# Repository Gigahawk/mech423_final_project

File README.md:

# LitePog

LitePog is a clone of the [Light Pong](https://www.playlightpong.com/) game.

## Folder Structure
- `firmware`: Code Composer Studio workspace containing firmware for the MSP430FR5739
- `mech`: SolidWorks mechanical CAD files
- `pcb`: KiCad electrical CAD files
- `wiring`: WireViz wire harness diagrams and diagrams.net system wiring diagram
- `proposal`: Initial project proposal for MECH 423 written in LaTeX
- `report`: Final project report for MECH 423 written in LaTeX
- `images`: Images for this readme

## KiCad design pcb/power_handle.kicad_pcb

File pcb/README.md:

# LitePog PCB

PCB files for LitePog

## Rev 2 Bring-Up Notes

The following notes refer to [pcb_rev2](https://github.com/Gigahawk/mech423_final_project/tree/pcb_rev2/pcb) (commit hash 8e8a57b).

Hardware has not been validated as of 2021-12-13, however it is likely that this revision will be functional out of the box.

## Rev 1 Bring-Up Notes

The following notes refer to [pcb_rev1](https://github.com/Gigahawk/mech423_final_project/tree/pcb_rev1/pcb) (commit hash f791dd6).

All hardware (with modifications) has been validated as of 2021-11-27.

### Logic Handle (assembled 2021-11-17)
Logic handle was assembled and tested over multiple days:
- 2021-11-17: Initial bring up and testing of all components
- 2021-11-24:
    - Validate Neopixel function with 3.3V logic level
    - Fix transistor connection for button LED

Notes:
- MCU appears to work fine
    - Can be programmed as expected
    - Resonator `Y1` not populated for now, likely not necessary
        - Firmware can rely entirely on DCO
- Power supply works fine
    - Produces 3.3V as expected
- Level shifter doesn't work
    - Level shifter U2 is designed to be connected between open-drain (or push-pull) pins, not to be connected directly to buttons or LEDs.
    - Solutions:
        - Remove/bypass the shifter (**Current solution as of 2021-11-17**)
            - The only strictly 5V level interface is the Neopixel strip, although it is fairly likely to work at 3.3V
            - All other IO is OK to run at 3.3V
            - *EDIT 2021-11-24: Neopixel strip works fine with 3.3V logic signals, level shifter has been removed, and all bypass jumpers set*
        - Use shifters with explicit transfer directions
            - Will need multiple chips, but this will allow all IO to be 5V
        - Only shift the Neopixel data line
            - Minimizes chips, ideal solution for next revision
- LED transistor `Q1` is wired incorrectly
    - Current always flows through body diode regardless of input
    - Solutions:
        - Short `LED-` and `LED1` (*Solution from 2021-11-17*):
            - This inverses the LED on polarity (Set `LED1` to let current flow, high to stop)
            - This sinks 20 mA into the GPIO pin, not ideal.
            - This may cause problems/uneven lighting across the interconnect due to voltage drop.
                - The transistor on the power PCB appears to be correct
        - Flip transistor on PCB (**Current solution as of 2021-11-24**)
            - Pins 1 and 2 need to be swapped (pins on same side of IC), which means pin 3 will be facing the other way. It just so happens that there is a ground pad at approximately the right distance away from the actual transistor footprint that would make this work (or some of the silkscreen can be scratched away)
            - *CORRECTION 2021-11-24: pins 2 and 3 need to be swapped, this was done by rotating IC 180 degrees.*
            *Pin 1 was left floating, which was connected back to R8 with a bodge wire.*
        - Fix transistor configuration in schematic(swap drain and source)
            - ideal solution for next revision
- *EDIT 2021-12-06: LED strip connector `JNPX1` should be moved towards the center by 0.5 to 1mm to avoid interference with the casing.*

### Power Handle
Power handle was assembled over multiple days:
- 2021-11-26: bring up and testing of critical components (boost, charging, protection, in that order)
- 2021-11-27: assemble misc components (connectors, battery holder, button circuitry)
- 2021-12-09: Final testing of safety features

Notes:
- Boost circuit works as designed, capable of producing high current (> 1A continuous for 10 seconds)
- Boost circuit can not be turned off
    - The datasheet for PAM2423 indicates that setting the `EN` pin low only disables the IC's boosting function, it does not turn off the output since there is a direct path from input to output via the inductor and diode.
    - Solutions:
        - Use switch to cut off input current (**Current solution as of 2021-11-26**)
            - Done by cutting the traces going to the input, and running wires to `SW1`.
                - `SW1` is already connected to `BATT+` to drive the `EN` pin, add an extra wire to allow high current flow
            - The EG1224 is only rated for 0.5A, finding higher current switches in this form factor is hard
                - EG2219 is a DPDT switch rated for 0.5A per pole, which can theoretically be combined for 1A total current, but this is still impractical because the input must provide more than 1A current at peak loads
                - Testing at 1A output current (~ 2A input current) seems to be fine (tested for ~10 seconds)
            - This is the simplest solution for this revision, since it does not require `EN` to be rewired, nor does it allow the boost converter to continually drain the battery from quiescent current.
            - There is a risk of arcing if switch is disconnected during high load, although this has not been observed, and should never happen in normal operation
        - Use switch to cut off output current
            - Similar issues to cutting off input current, although current requirements on the output are lower
            - Boost converter will be constantly on, and drawing quiescent current from battery
            - There is a risk of arcing if switch is disconnected during high load, although this has not been observed, and should never happen in normal operation
        - Use MOSFET to switch input current
            - Switch input from high side using a PMOS
            - Ideal solution for next revision
- Charging circuit appears to work as expected
    - LED comes on when plugged in and battery is below max voltage
    - LED turns off when max voltage is reached
    - *EDIT 2021-12-09: Full discharge and charge cycle tested. Charging cutoff occurred at 4.2V as expected*
- Protection circuit appears to work as expected
    - Datasheet for BQ2970 indicates that it must be bootstrapped the first time by connecting a charger to the battery, which was observed
    - *Note: protection features are largely untested*
        - Over discharge current protection is set high enough that it cannot trip
            - This is intentional, we want to allow the battery to provide as much current as necessary for the boost converter
            - A battery capable of providing the necessary current without overheating is being used
        - Short circuit protection is untested
            - This would involve shorting `BATT+` to ground, which is unlikely to happen in regular operation
            - This safety feature is typically intended for standalone battery protection boards that provide user accessible output terminals that could be accidentally shorted
        - Under voltage protection is untested
            - It is time-consuming to wait for the battery to completely drain while monitoring the voltage to ensure that the cutoff protection works.
            - Periodic checking of the battery voltage during firmware development should take place to ensure the battery voltage is within safe levels
            - *EDIT 2021-12-09: Full discharge and charge cycle tested.*
                - Output was shut off at a safe voltage (VBAT ~2.9V when measured, but it may have risen slightly due to hysteresis)
                - It is unclear which chip is actually responsible for cutting off the battery, both the PAM2423 boost converter and the BQ29703DSET protection chip is rated for an under voltage lockout of 2.5V, although it is likely both chips are working as expected.
        - Over voltage protection is untested
            - The charging circuit stops charging the battery prior to the over voltage protection threshold
        - Over charge current protection is untested
            - The charge current of the charging circuit is fixed at 500mA, and should never be high enough to trigger over charge current protection
- Bypass diode `D2` is left unpopulated
    - Theoretically it should be safe to populate, however it is unknown if this will cause adverse behavior with the boost circuit.
    - Populating this diode will prevent the output from being turned off with the switch when `VBUS` is present
- Aluminum capacitors `C10` and `C1` are not structurally sound
    - Should be reinforced with hot glue

### Button Harness (Assembled 2021-11-24)
- Works as expected

### Neopixel Strip (Assembled 2021-11-24)
- Removing provided connectors is rather hard
    - Nearly damaged the pads while removing old joints
    - Simpler solution for next revision is to order more LEDs than required and cut off first one to access unsoldered pads

### Interconnect Harness (Assembled 2021-11-24)
- Works as expected
- Very time-consuming to assemble, set aside more time to do this next revision

### Mock Power Handle (Assembled 2021-11-27)
- Assembled board with bypass diode `D2` connecting the USB connector directly to `VCC`, and button circuitry for use in firmware testing.

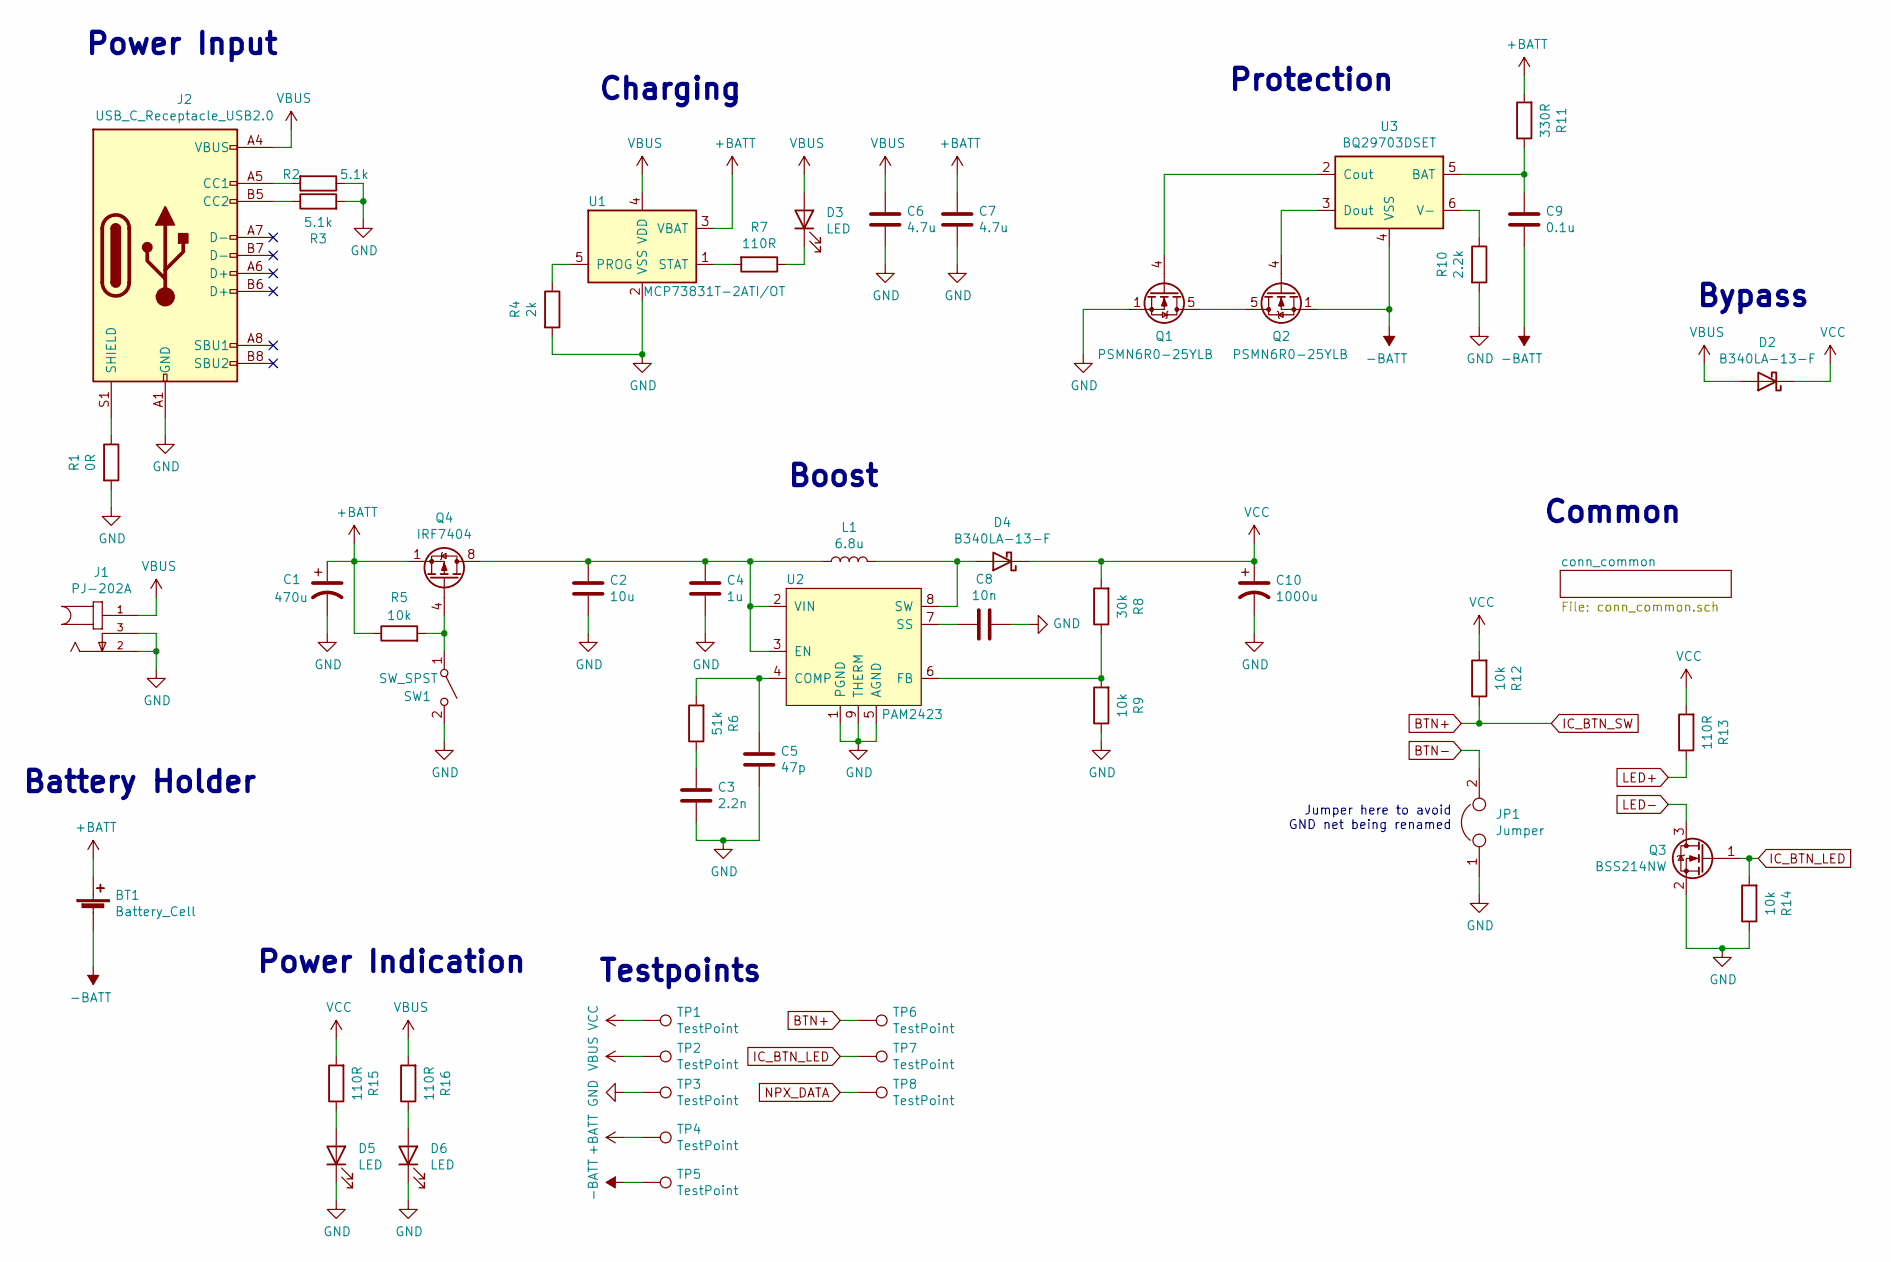
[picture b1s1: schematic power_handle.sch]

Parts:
BT1: Battery_Cell; BatteryHolder_Keystone_1042_1x18650; Digikey 36-1042-ND
C1: 470u; CP_Elec_8x10; Digikey 732-6451-1-ND
C2: 10u; C_0805_2012Metric; Digikey 1276-6456-1-ND
C3: 2.2n; C_0805_2012Metric; Digikey 1276-2484-1-ND
C4: 1u; C_0805_2012Metric; Digikey 1276-1026-1-ND
C5: 47p; C_0805_2012Metric; Digikey 709-1175-1-ND
C6, C7: 4.7u; C_0805_2012Metric; Digikey 1276-1259-1-ND
C8: 10n; C_0805_2012Metric; Digikey 478-1383-1-ND
C9: 0.1u; C_0805_2012Metric; Digikey 478-10836-1-ND
C10: 1000u; CP_Elec_10x12.6; Digikey 493-13738-1-ND
D2, D4: B340LA-13-F; D_SMA; Digikey 641-1258-1-ND
D3, D5, D6: LED; LED_0603_1608Metric; Digikey 160-1832-1-ND
J1: PJ-202A; CUI_PJ-202A; PART_REV 1.02; Digikey CP-202A-ND
J2: USB_C_Receptacle_USB2.0; UJC-HP-3-SMT-TR; Digikey 2223-UJC-HP-3-SMT-CT-ND
JP1: Jumper; SolderJumper-2_P1.3mm_Bridged2Bar_Pad1.0x1.5mm
L1: 6.8u; ASPI-0630LR-6R8M-T15; Digikey 535-13041-1-ND
Q1, Q2: PSMN6R0-25YLB; LFPAK56; Digikey 1727-6497-1-ND
Q3: BSS214NW; SOT-323_SC-70; Digikey BSS214NWH6327XTSA1CT-ND
Q4: IRF7404; SOIC-8_3.9x4.9mm_P1.27mm; Digikey IRF7404PBFCT-ND
R1: 0R; R_0805_2012Metric; Digikey RMCF0805ZT0R00CT-ND
R2, R3: 5.1k; R_0805_2012Metric; Digikey A126379CT-ND
R4: 2k; R_0805_2012Metric; Digikey RG20N2.0KWCT-ND
R5, R9, R12, R14: 10k; R_0805_2012Metric; Digikey RMCF0805JT10K0CT-ND
R6: 51k; R_0805_2012Metric; Digikey A126373CT-ND
R7, R13, R15, R16: 110R; R_0805_2012Metric; Digikey RMCF0805JT110RCT-ND
R8: 30k; R_0805_2012Metric; Digikey 13-RT0805FRE0730KLCT-ND
R10: 2.2k; R_0805_2012Metric; Digikey A106060CT-ND
R11: 330R; R_0805_2012Metric; Digikey A130131CT-ND
SW1: SW_SPST; SW_E-Switch_EG1224_SPDT_Angled; Digikey EG2585-ND
TP1, TP2, TP3, TP4, TP5, TP6, TP7, TP8: TestPoint; TestPoint_Pad_2.0x2.0mm
U1: MCP73831T-2ATI/OT; SOT-23-5; Digikey MCP73831T-2ATI/OTCT-ND
U2: PAM2423; HSOP-8-1EP_3.9x4.9mm_P1.27mm_EP2.41x3.1mm_HandSolderThermal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; Digikey PAM2423AECADJRDICT-ND
U3: BQ29703DSET; WSON-6_1.5x1.5mm_P0.5mm; Digikey 296-37960-1-ND

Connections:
+BATT: BT1.1 (+), C1.1, C7.1, Q4.1 (S), Q4.2 (S), Q4.3 (S), R5.1, R11.2, TP4.1, U1.3 (VBAT)
-BATT: BT1.2 (-), C9.2, Q2.1 (S), Q2.2 (S), Q2.3 (S), TP5.1, U3.4 (VSS)
BTN+: R12.1, TP6.1; also elsewhere on the board
BTN-: JP1.2; also elsewhere on the board
GND: C1.2, C2.1, C3.1, C4.1, C5.2, C6.2, C7.2, C8.1, C10.2, D5.1 (K), D6.1 (K), J1.2, J1.3, J2.A1 (GND), J2.A12 (GND), J2.B1 (GND), J2.B12 (GND), JP1.1, Q1.1 (S), Q1.2 (S), Q1.3 (S), Q3.2 (S), R1.2, R2.1, R3.2, R4.2, R9.1, R10.2, R14.1, SW1.2 (B), TP3.1, U1.2 (VSS), U2.1 (PGND), U2.5 (AGND), U2.9 (THERM); also elsewhere on the board
IC_BTN_LED: Q3.1 (G), R14.2, TP7.1; also elsewhere on the board
LED+: R13.1; also elsewhere on the board
LED-: Q3.3 (D); also elsewhere on the board
NPX_DATA: TP8.1; also elsewhere on the board
unnamed: C2.2, C4.2, L1.1, Q4.5 (D), Q4.6 (D), Q4.7 (D), Q4.8 (D), U2.2 (VIN), U2.3 (EN)
unnamed: C3.2, R6.1
unnamed: C5.1, R6.2, U2.4 (COMP)
unnamed: C8.2, U2.7 (SS)
unnamed: C9.1, R11.1, U3.5 (BAT)
unnamed: D3.1 (K), R7.1
unnamed: D4.2 (A), L1.2, U2.8 (SW)
unnamed: D5.2 (A), R15.1
unnamed: D6.2 (A), R16.1
unnamed: J2.A5 (CC1), R2.2
unnamed: J2.B5 (CC2), R3.1
unnamed: J2.S1 (SHIELD), R1.1
unnamed: Q1.4 (G), U3.2 (Cout)
unnamed: Q1.5 (D), Q2.5 (D)
unnamed: Q2.4 (G), U3.3 (Dout)
unnamed: Q4.4 (G), R5.2, SW1.1 (A)
unnamed: R4.1, U1.5 (PROG)
unnamed: R7.2, U1.1 (STAT)
unnamed: R8.1, R9.2, U2.6 (FB)
unnamed: R10.1, U3.6 (V-)
VBUS: C6.1, D2.2 (A), D3.2 (A), J1.1, J2.A4 (VBUS), J2.A9 (VBUS), J2.B4 (VBUS), J2.B9 (VBUS), R16.2, TP2.1, U1.4 (VDD)
VCC: C10.1, D2.1 (K), D4.1 (K), R8.2, R12.2, R13.2, R15.2, TP1.1; also elsewhere on the board

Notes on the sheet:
Power Input
Charging
Protection
Boost
Battery Holder
Common
Power Indication
Testpoints
Jumper here to avoid GND net being renamed
Bypass

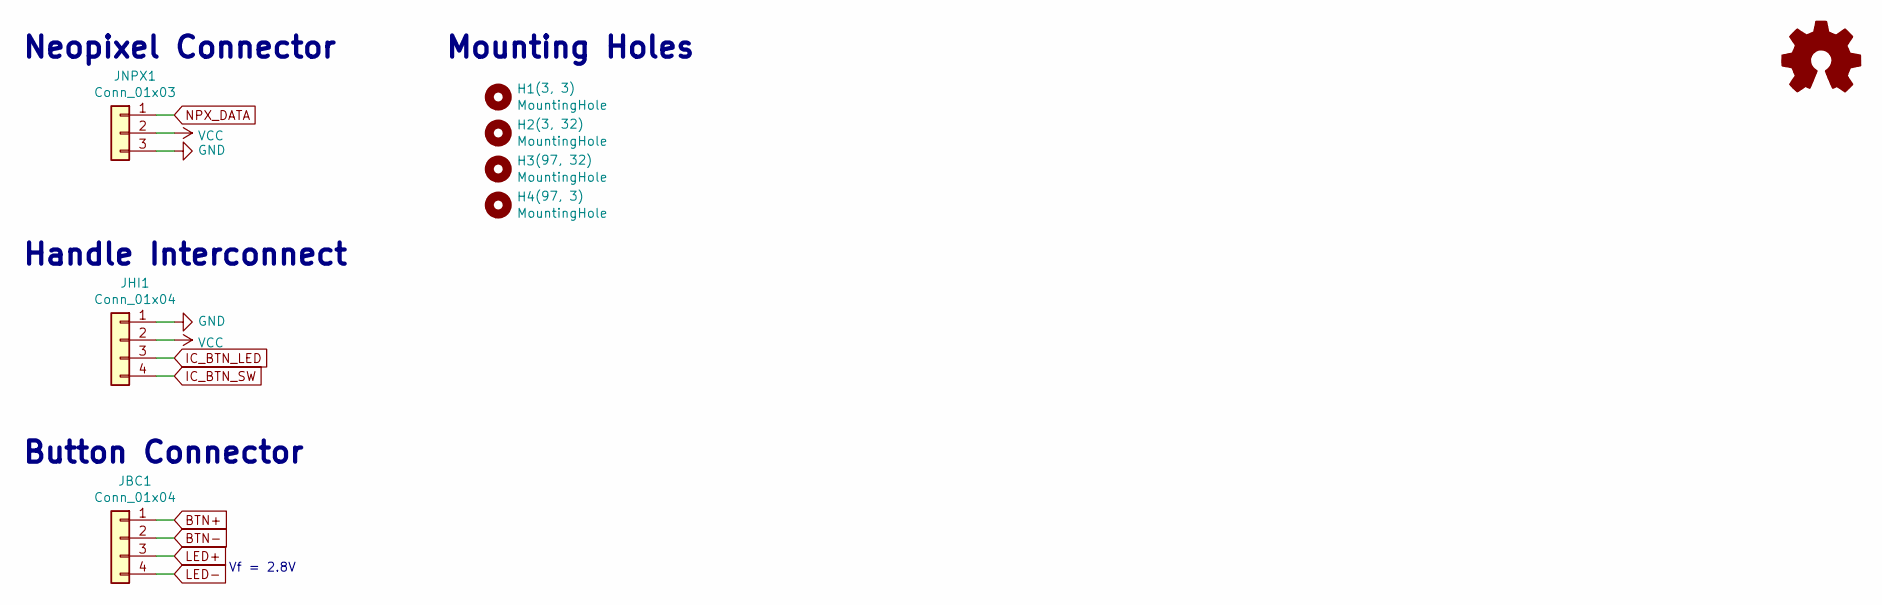
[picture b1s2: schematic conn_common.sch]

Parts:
H1, H2, H3, H4: MountingHole; MountingHole_2.7mm_M2.5
JBC1: Conn_01x04; JST_SH_SM04B-SRSS-TB_1x04-1MP_P1.00mm_Horizontal; Digikey SM04B-SRSS-TB
JHI1: Conn_01x04; JST_SH_SM04B-SRSS-TB_1x04-1MP_P1.00mm_Horizontal; Digikey SM04B-SRSS-TB
JNPX1: Conn_01x03; JST_PH_S3B-PH-SM4-TB_1x03-1MP_P2.00mm_Horizontal; Digikey 455-1750-1-ND
LOGO1: Logo_Open_Hardware_Small; OSHW-Logo_5.7x6mm_SilkScreen

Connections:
BTN+: JBC1.1, JHI1.4; also elsewhere on the board
BTN-: JBC1.2; also elsewhere on the board
GND: JHI1.1, JNPX1.3; also elsewhere on the board
IC_BTN_LED: JHI1.3; also elsewhere on the board
LED+: JBC1.3; also elsewhere on the board
LED-: JBC1.4; also elsewhere on the board
NPX_DATA: JNPX1.1; also elsewhere on the board
VCC: JHI1.2, JNPX1.2; also elsewhere on the board

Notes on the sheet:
Neopixel Connector
Handle Interconnect
Button Connector
Vf = 2.8V
Mounting Holes

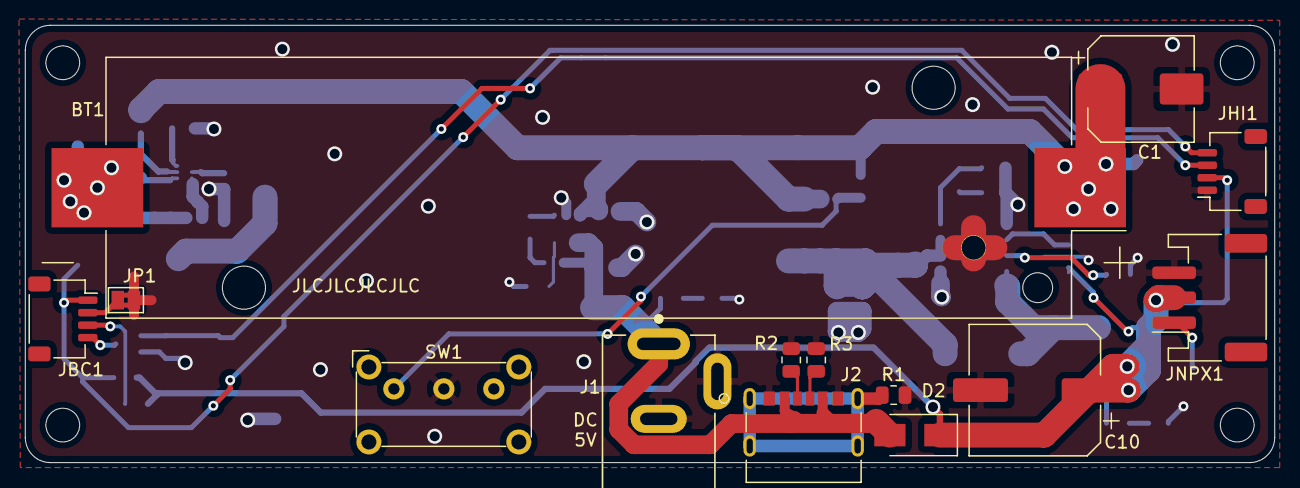
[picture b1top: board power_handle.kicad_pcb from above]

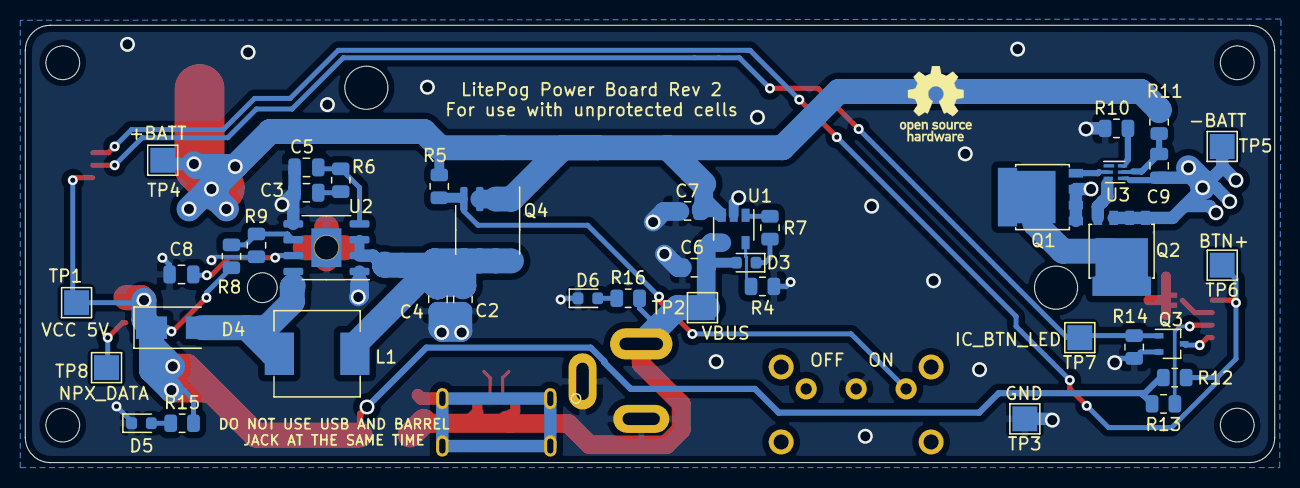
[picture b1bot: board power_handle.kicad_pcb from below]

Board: 2 copper layers, 100.0 x 35.0 mm, 60 parts (42 on the bottom side), 31 nets.

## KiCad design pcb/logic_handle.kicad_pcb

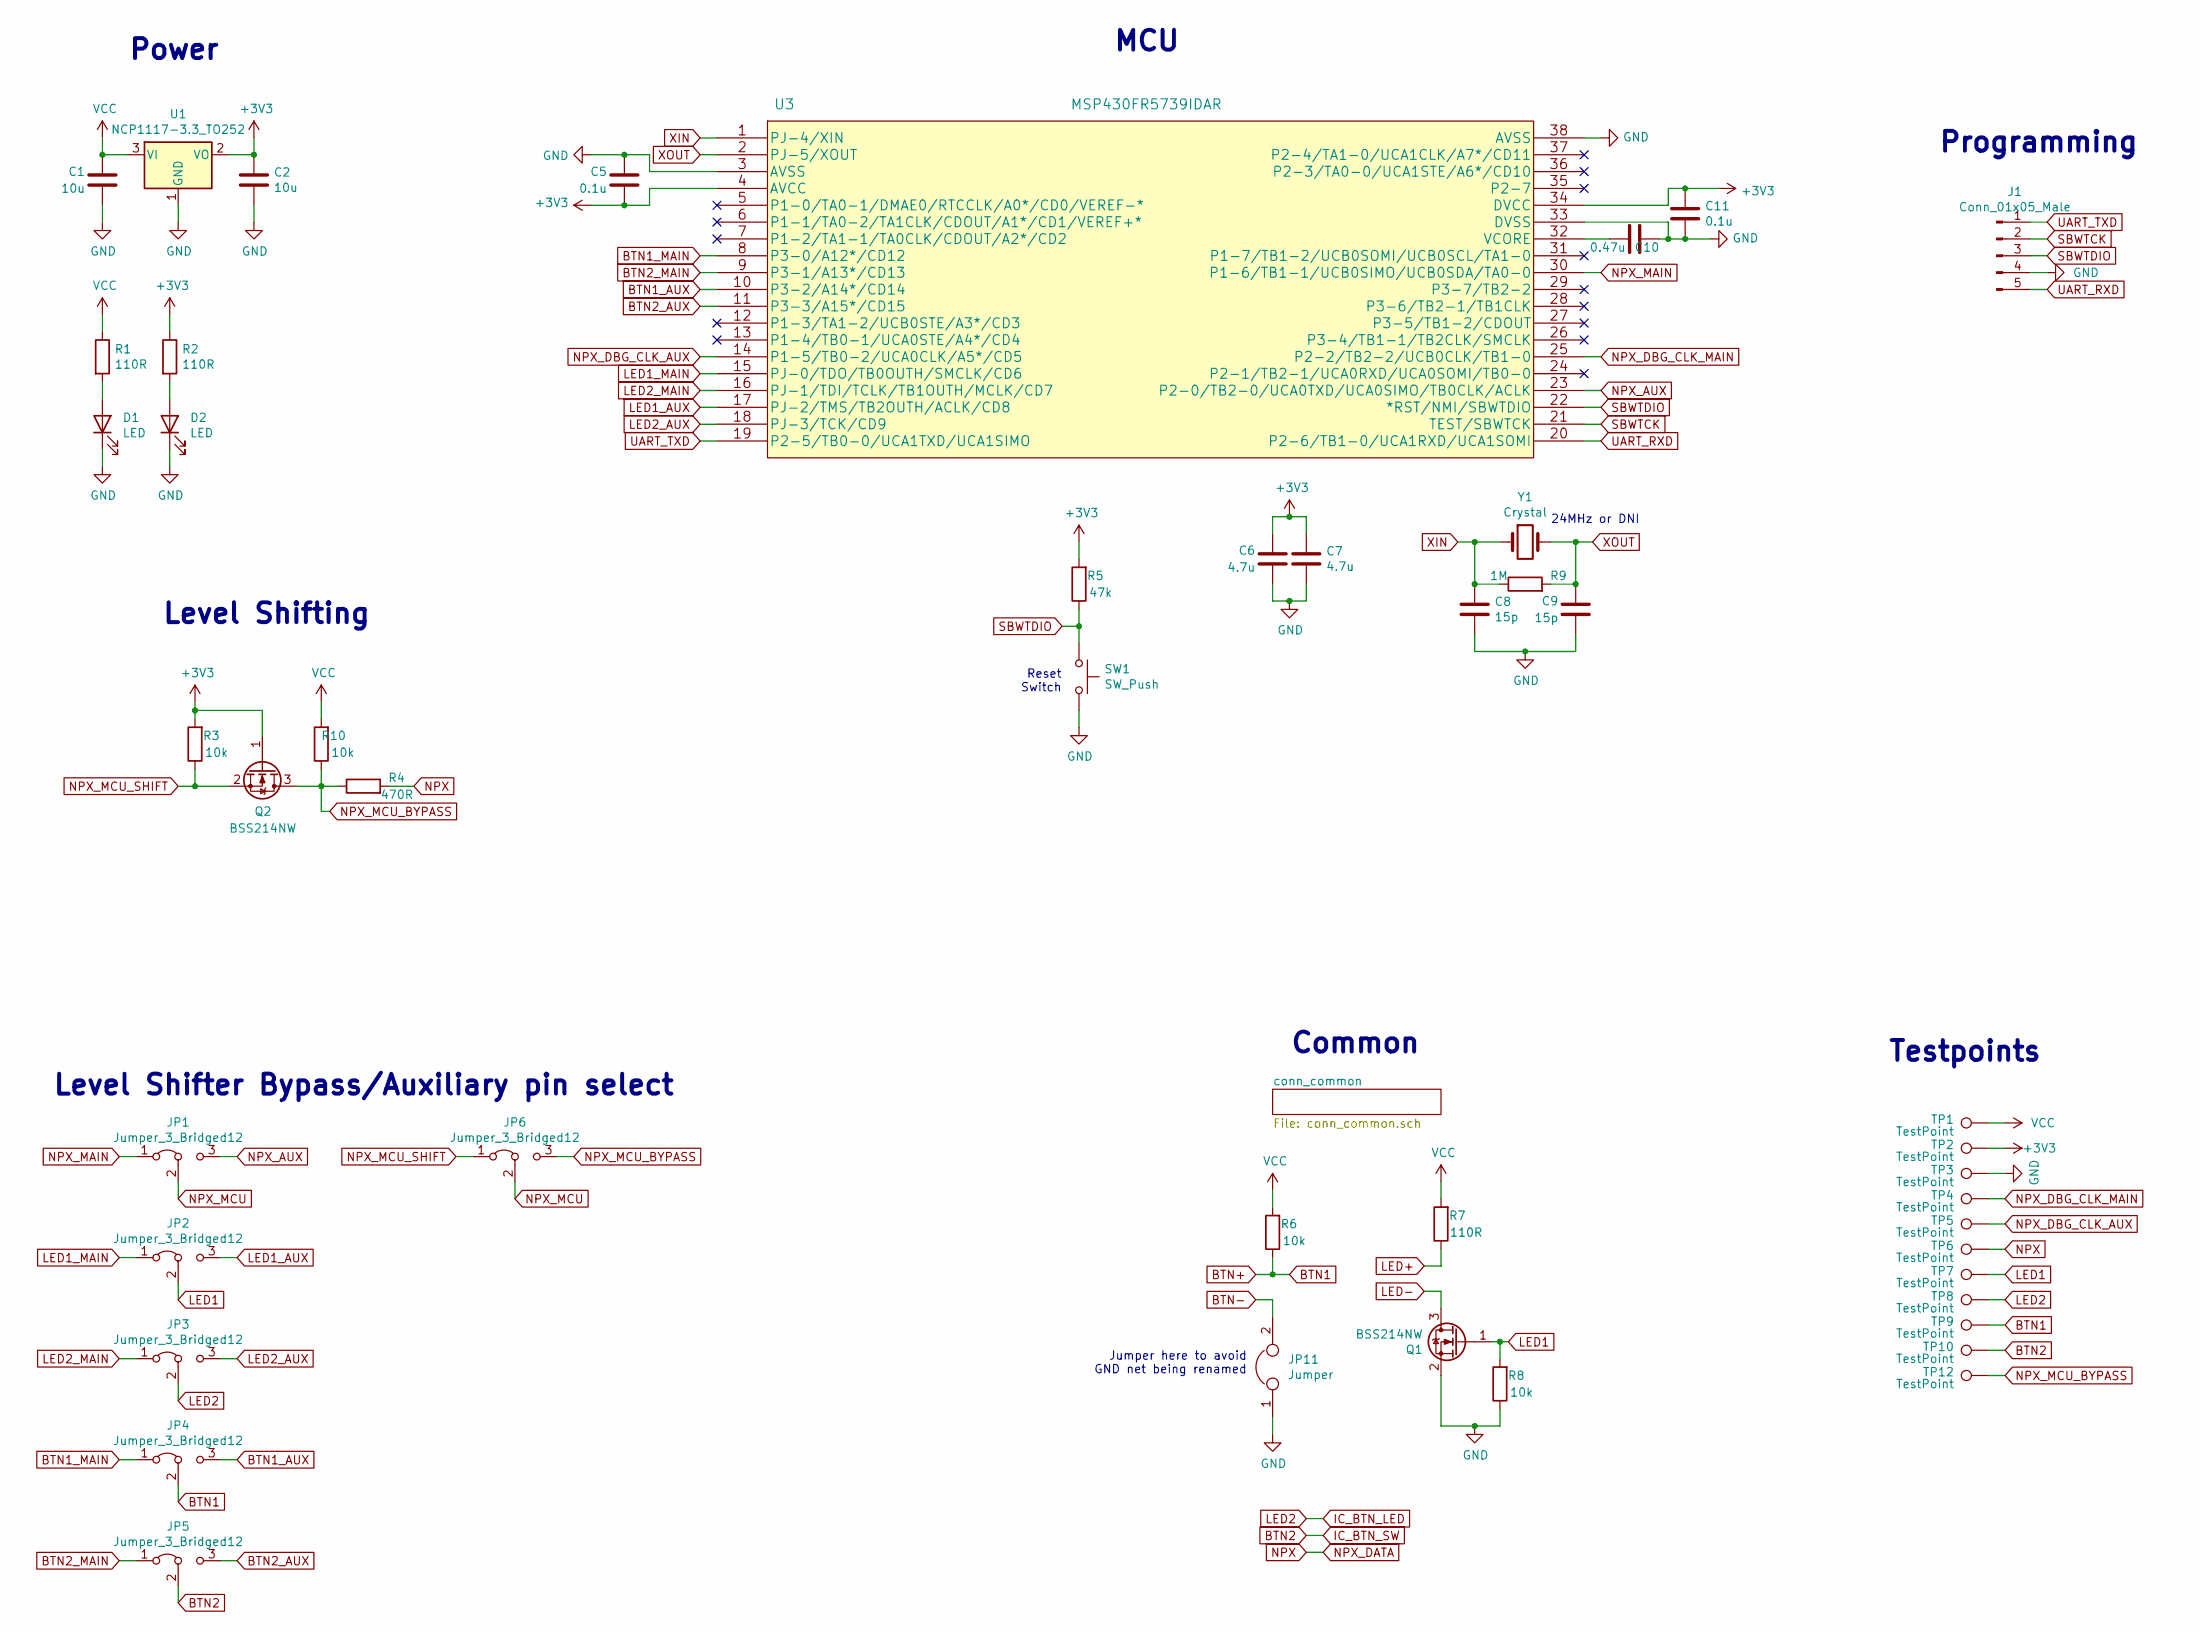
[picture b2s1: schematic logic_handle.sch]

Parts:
C1, C2: 10u; C_0805_2012Metric; Digikey 1276-6456-1-ND
C5, C11: 0.1u; C_0805_2012Metric; Digikey 478-10836-1-ND
C6, C7: 4.7u; C_0805_2012Metric; Digikey 1276-1259-1-ND
C8, C9: 15p; C_0805_2012Metric; Digikey 478-1306-1-ND
C10: 0.47u; C_0805_2012Metric; Digikey 478-10438-1-ND
D1, D2: LED; LED_0603_1608Metric; Digikey 160-1832-1-ND
J1: Conn_01x05_Male; PinHeader_1x05_P2.54mm_Vertical
JP1, JP2, JP3, JP4, JP5, JP6: Jumper_3_Bridged12; SolderJumper-3_P1.3mm_Bridged2Bar12_Pad1.0x1.5mm
JP11: Jumper; SolderJumper-2_P1.3mm_Bridged2Bar_Pad1.0x1.5mm
Q1, Q2: BSS214NW; SOT-323_SC-70; Digikey BSS214NWH6327XTSA1CT-ND
R1, R2, R7: 110R; R_0805_2012Metric; Digikey RMCF0805JT110RCT-ND
R3, R6, R8, R10: 10k; R_0805_2012Metric; Digikey RMCF0805JT10K0CT-ND
R4: 470R; R_0805_2012Metric; Digikey A129745CT-ND
R5: 47k; R_0805_2012Metric; Digikey A130144CT-ND
R9: 1M; R_0805_2012Metric; Digikey A106058CT-ND
SW1: SW_Push; SW_SPST_TL3342; Digikey EG5470CT-ND
TP1, TP2, TP3, TP4, TP5, TP6, TP7, TP8, TP9, TP10, TP12: TestPoint; TestPoint_Pad_2.0x2.0mm
U1: NCP1117-3.3_TO252; TO-252-2; Digikey NCP1117ST33T3GOSCT-ND
U3: MSP430FR5739IDAR; Digikey 296-29235-1-ND
Y1: Crystal; Crystal_SMD_AWSZT-CV-2Pin_3.7x3.1mm; Digikey 535-10028-2-ND

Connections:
+3V3: C2.1, C5.1, C6.2, C7.1, C11.1, Q2.1 (G), R2.1, R3.2, R5.2, TP2.1, U1.2 (VO), U3.4 (AVCC), U3.34 (DVCC)
BTN1_AUX: JP4.3 (B), U3.10 (P3-2/A14*/CD14)
BTN1_MAIN: JP4.1 (A), U3.8 (P3-0/A12*/CD12)
BTN2: JP5.2 (C), TP10.1; also elsewhere on the board
BTN2_AUX: JP5.3 (B), U3.11 (P3-3/A15*/CD15)
BTN2_MAIN: JP5.1 (A), U3.9 (P3-1/A13*/CD13)
BTN+: JP4.2 (C), R6.1, TP9.1; also elsewhere on the board
BTN-: JP11.2; also elsewhere on the board
GND: C1.1, C2.2, C5.2, C6.1, C7.2, C8.2, C9.1, C10.2, C11.2, D1.1 (K), D2.1 (K), J1.4, JP11.1, Q1.2 (S), R8.1, SW1.2, TP3.1, U1.1 (GND), U3.3 (AVSS), U3.33 (DVSS), U3.38 (AVSS); also elsewhere on the board
IC_BTN_LED: JP3.2 (C), TP8.1; also elsewhere on the board
LED1: JP2.2 (C), Q1.1 (G), R8.2, TP7.1
LED1_AUX: JP2.3 (B), U3.17 (PJ-2/TMS/TB2OUTH/ACLK/CD8)
LED1_MAIN: JP2.1 (A), U3.15 (PJ-0/TDO/TB0OUTH/SMCLK/CD6)
LED2_AUX: JP3.3 (B), U3.18 (PJ-3/TCK/CD9)
LED2_MAIN: JP3.1 (A), U3.16 (PJ-1/TDI/TCLK/TB1OUTH/MCLK/CD7)
LED+: R7.1; also elsewhere on the board
LED-: Q1.3 (D); also elsewhere on the board
NPX: R4.2, TP6.1; also elsewhere on the board
NPX_AUX: JP1.3 (B), U3.23 (P2-0/TB2-0/UCA0TXD/UCA0SIMO/TB0CLK/ACLK)
NPX_DBG_CLK_AUX: TP5.1, U3.14 (P1-5/TB0-2/UCA0CLK/A5*/CD5)
NPX_DBG_CLK_MAIN: TP4.1, U3.25 (P2-2/TB2-2/UCB0CLK/TB1-0)
NPX_MAIN: JP1.1 (A), U3.30 (P1-6/TB1-1/UCB0SIMO/UCB0SDA/TA0-0)
NPX_MCU: JP1.2 (C), JP6.2 (C)
NPX_MCU_BYPASS: JP6.3 (B), Q2.3 (D), R4.1, R10.1, TP12.1
NPX_MCU_SHIFT: JP6.1 (A), Q2.2 (S), R3.1
unnamed: C10.1, U3.32 (VCORE)
unnamed: D1.2 (A), R1.2
unnamed: D2.2 (A), R2.2
SBWTCK: J1.2, U3.21 (TEST/SBWTCK)
SBWTDIO: J1.3, R5.1, SW1.1, U3.22 (*RST/NMI/SBWTDIO)
UART_RXD: J1.5, U3.20 (P2-6/TB1-0/UCA1RXD/UCA1SOMI)
UART_TXD: J1.1, U3.19 (P2-5/TB0-0/UCA1TXD/UCA1SIMO)
VCC: C1.2, R1.1, R6.2, R7.2, R10.2, TP1.1, U1.3 (VI); also elsewhere on the board
XIN: C8.1, R9.1, U3.1 (PJ-4/XIN), Y1.1
XOUT: C9.2, R9.2, U3.2 (PJ-5/XOUT), Y1.2

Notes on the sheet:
Level Shifting
MCU
Power
Reset Switch
Level Shifter Bypass/Auxiliary pin select
Jumper here to avoid GND net being renamed
Programming
24MHz or DNI
Common
Testpoints

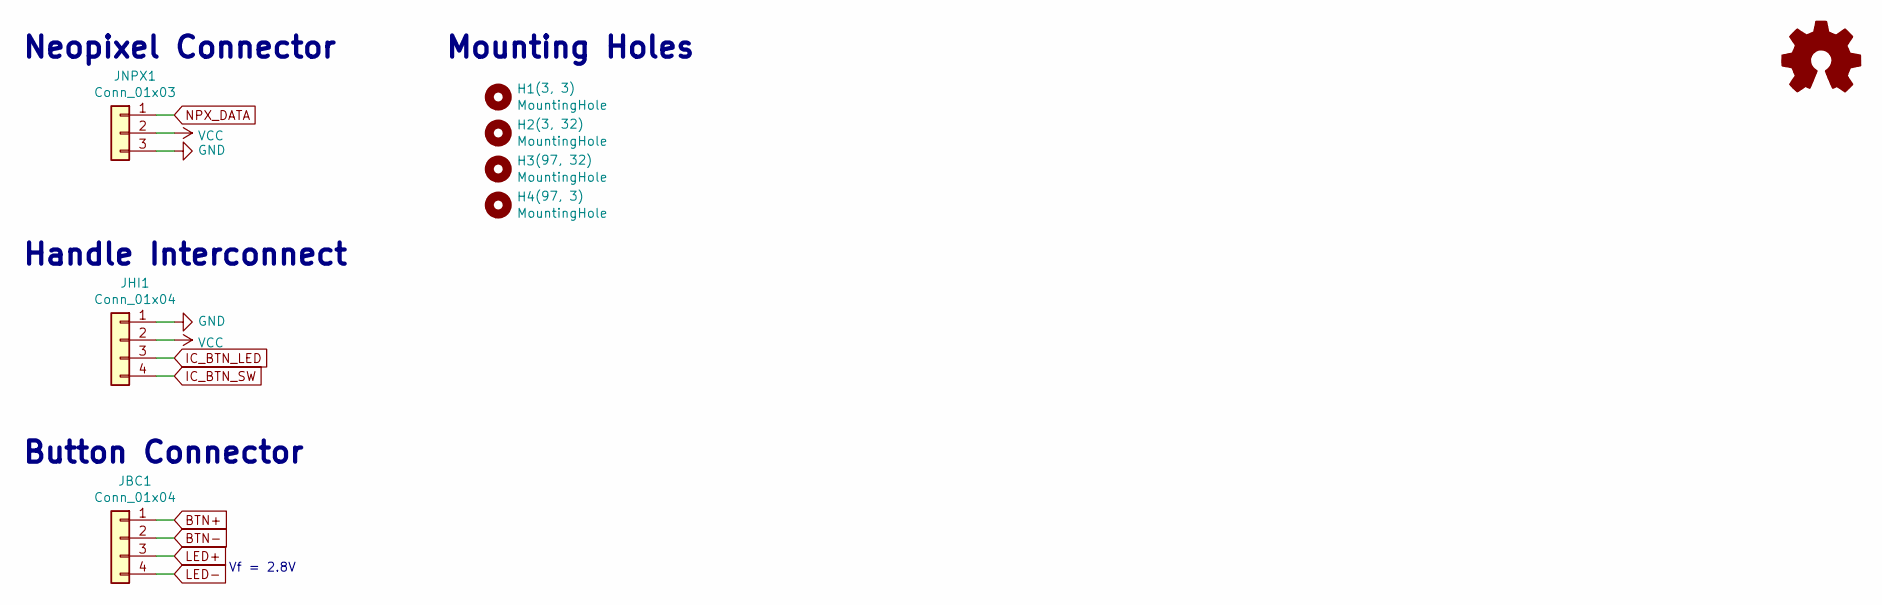
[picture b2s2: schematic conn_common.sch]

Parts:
H1, H2, H3, H4: MountingHole; MountingHole_2.7mm_M2.5
JBC1: Conn_01x04; JST_SH_SM04B-SRSS-TB_1x04-1MP_P1.00mm_Horizontal; Digikey SM04B-SRSS-TB
JHI1: Conn_01x04; JST_SH_SM04B-SRSS-TB_1x04-1MP_P1.00mm_Horizontal; Digikey SM04B-SRSS-TB
JNPX1: Conn_01x03; JST_PH_S3B-PH-SM4-TB_1x03-1MP_P2.00mm_Horizontal; Digikey 455-1750-1-ND
LOGO1: Logo_Open_Hardware_Small; OSHW-Logo_5.7x6mm_SilkScreen

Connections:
BTN2: JHI1.4; also elsewhere on the board
BTN+: JBC1.1; also elsewhere on the board
BTN-: JBC1.2; also elsewhere on the board
GND: JHI1.1, JNPX1.3; also elsewhere on the board
IC_BTN_LED: JHI1.3; also elsewhere on the board
LED+: JBC1.3; also elsewhere on the board
LED-: JBC1.4; also elsewhere on the board
NPX: JNPX1.1; also elsewhere on the board
VCC: JHI1.2, JNPX1.2; also elsewhere on the board

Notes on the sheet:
Neopixel Connector
Handle Interconnect
Button Connector
Vf = 2.8V
Mounting Holes

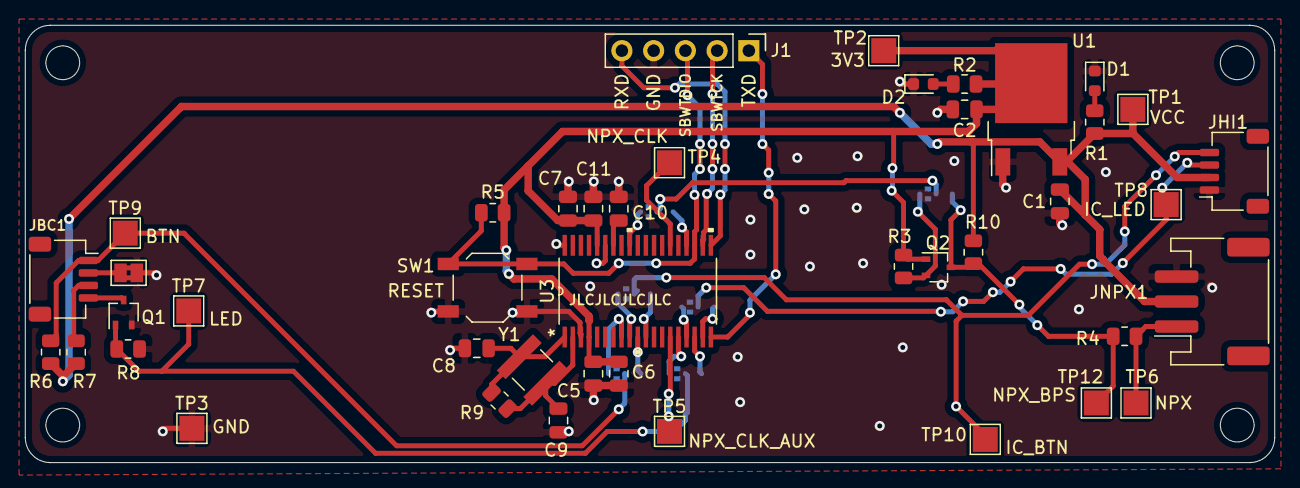
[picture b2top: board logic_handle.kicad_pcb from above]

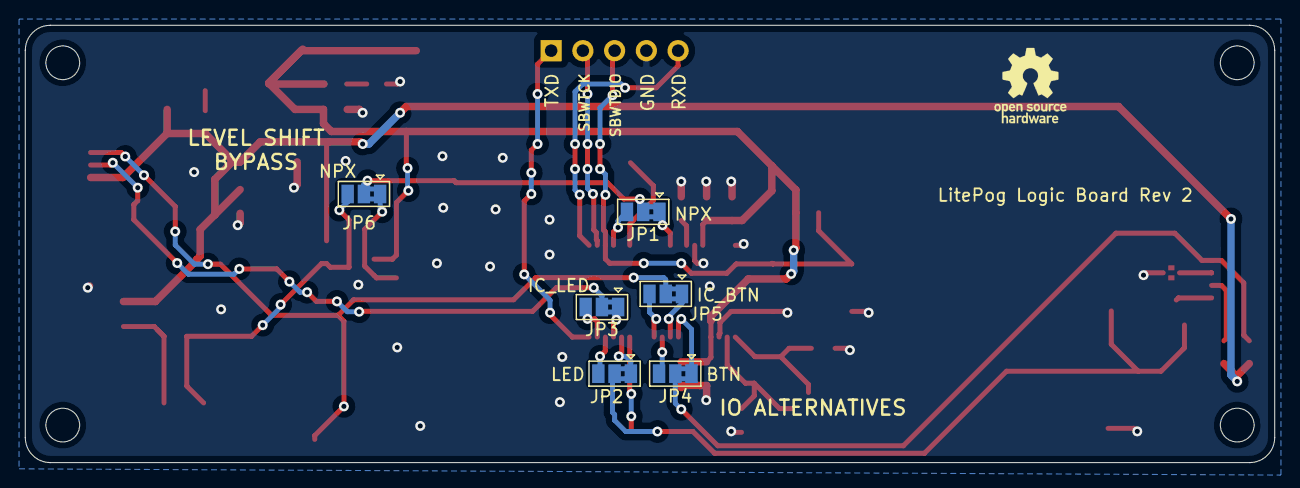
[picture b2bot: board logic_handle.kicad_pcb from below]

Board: 2 copper layers, 100.0 x 35.0 mm, 54 parts (7 on the bottom side), 35 nets.

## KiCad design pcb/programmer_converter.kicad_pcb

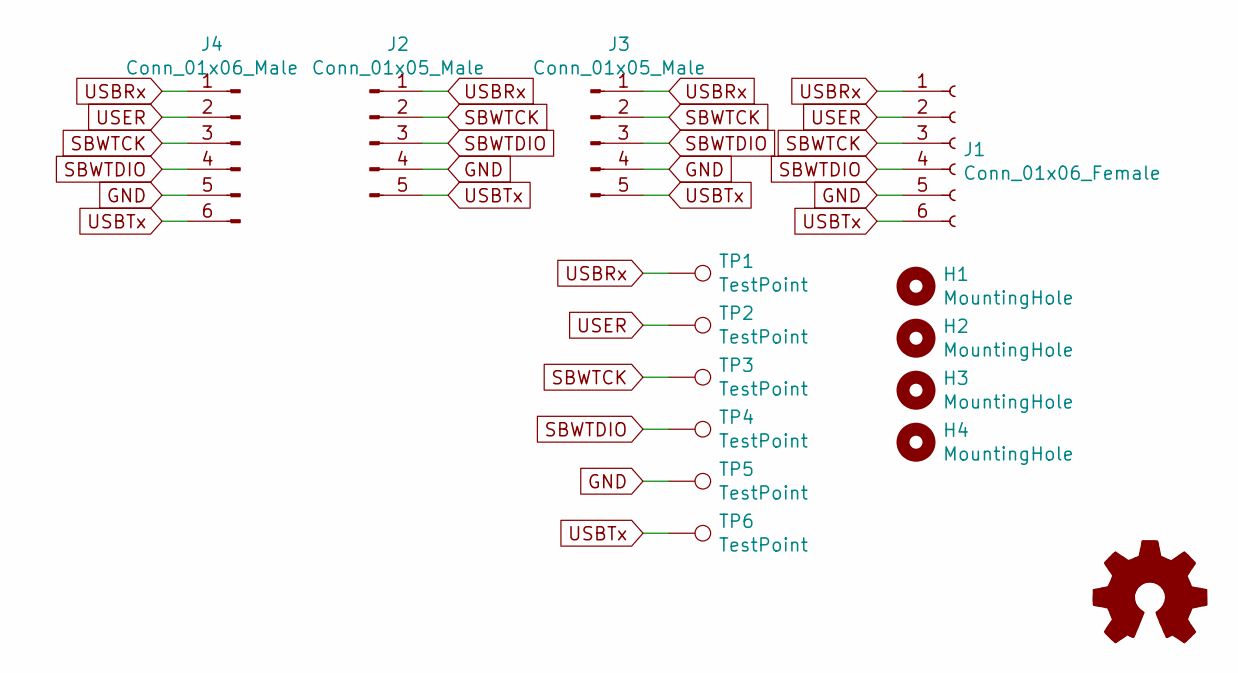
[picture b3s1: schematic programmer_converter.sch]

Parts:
H1, H2, H3, H4: MountingHole; MountingHole_2.7mm_M2.5
J1: Conn_01x06_Female; 851-87-006-20-001101
J2, J3: Conn_01x05_Male; PinHeader_1x05_P2.54mm_Vertical
J4: Conn_01x06_Male; PinHeader_1x06_P1.27mm_Horizontal
LOGO1: Logo_Open_Hardware_Small; OSHW-Logo_5.7x6mm_SilkScreen
TP1, TP2, TP3, TP4, TP5, TP6: TestPoint; TestPoint_Pad_2.0x2.0mm

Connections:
GND: J1.5, J2.4, J3.4, J4.5, TP5.1
SBWTCK: J1.3, J2.2, J3.2, J4.3, TP3.1
SBWTDIO: J1.4, J2.3, J3.3, J4.4, TP4.1
USBRx: J1.1, J2.1, J3.1, J4.1, TP1.1
USBTx: J1.6, J2.5, J3.5, J4.6, TP6.1
USER: J1.2, J4.2, TP2.1

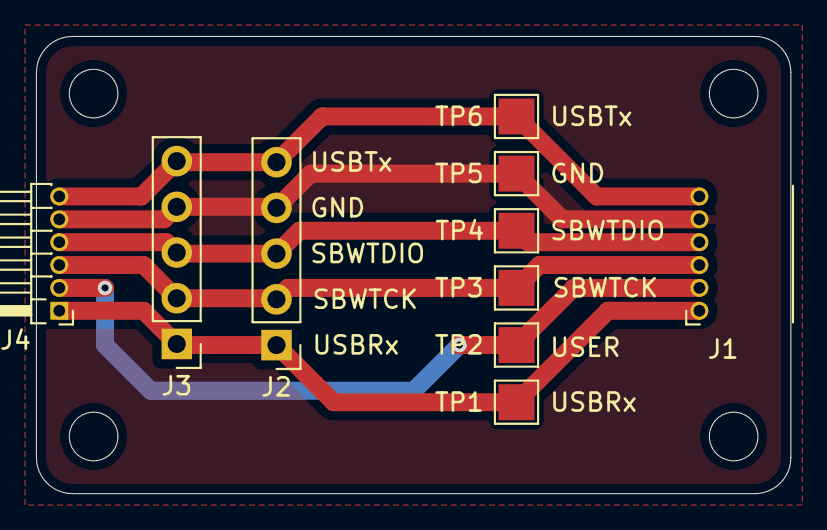
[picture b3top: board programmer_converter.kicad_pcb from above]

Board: 2 copper layers, 41.9 x 25.4 mm, 15 parts (1 on the bottom side), 6 nets.

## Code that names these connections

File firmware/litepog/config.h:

/*
 * config.h
 *
 *  Created on: Nov 16, 2021
 *      Author: Jasper
 */

#ifndef CONFIG_H_
#define CONFIG_H_

// Number of LEDs in Neopixel strip
#define NPX_NUM_LEDS 30

// Index of middle LED
#define NPX_MID_IDX (NPX_NUM_LEDS/2)

// True if even number of LEDs
#define NPX_EVEN_LEDS (!(NPX_NUM_LEDS % 2))

// Seed for pseudo-random number generator
#define PRNG_SEED 0xB00B

// Time to wait between allowing button edges during game select
#define GAME_SELECT_DEBOUNCE_TIME 20

// Width of game selection menu indicator
#define GAME_SELECT_WIDTH 6

// Time between demo animation frames
#define DEMO_INTERVAL 10

// Frame divisor for pong demo animation
#define DEMO_PONG_INTERVAL_DIV 4

// Frame divisor for ping pong demo animation
#define DEMO_PINGPONG_INTERVAL_DIV 4

// Frame divisor for tug o' war demo animation
#define DEMO_TUGOWAR_INTERVAL_DIV 2

// Chance of ball being returned each frame of ping pong demo animation (1/N)
#define DEMO_PINGPONG_RETURN_RATE 9

// Width of the demo animation
#define DEMO_WIDTH 8

#define DEMO_MIN_IDX (NPX_MID_IDX - DEMO_WIDTH/2)
#define DEMO_MAX_IDX (NPX_MID_IDX + DEMO_WIDTH/2 - ((DEMO_WIDTH + 1) % 2))

// Time between countdown ticks
#define COUNTDOWN_INTERVAL 700

// Number of LEDs lit up for each countdown tick
#define COUNTDOWN_LED_WIDTH (1 + NPX_EVEN_LEDS)

// Number of countdown ticks before game start
#define COUNTDOWN_NUMBER 3

#define COUNTDOWN_MIN_IDX (NPX_MID_IDX - ((COUNTDOWN_NUMBER - 1)*COUNTDOWN_LED_WIDTH + NPX_EVEN_LEDS))
#define COUNTDOWN_MAX_IDX (NPX_MID_IDX + (COUNTDOWN_NUMBER - 1)*COUNTDOWN_LED_WIDTH)

// Brightness of ball return zones
#define RETURN_ZONE_BRIGHTNESS 15

// Initial time between ball events for pong
#define PONG_BALL_INTERVAL_START 70

// Amount of speedup after each rally for pong
#define PONG_BALL_INTERVAL_SPEEDUP 5

// Minimum interval time (max ball speed) for pong
#define PONG_BALL_INTERVAL_MIN 40

// Size of return zone for pong
#define PONG_RETURN_ZONE_WIDTH 3

// Initial time between ball events for pong
#define PINGPONG_BALL_INTERVAL_START 70

// Amount of speedup after each rally for pong
#define PINGPONG_BALL_INTERVAL_SPEEDUP 5

// Minimum interval time (max ball speed) for pong
#define PINGPONG_BALL_INTERVAL_MIN 10

// Size of return zone for pong
#define PINGPONG_RETURN_ZONE_WIDTH (NPX_MID_IDX - NPX_EVEN_LEDS)

// Debounce time for ping pong button reads
#define PINGPONG_DEBOUNCE_TIME 3

// Debounce time for tug o' war button reads
#define TUGOWAR_DEBOUNCE_TIME 3

// Time between winner animation frames
#define WINNER_INTERVAL 300

// Number of LEDs to flash per side
#define WINNER_LED_WIDTH 3

// Number of times the winner animation flashes
#define WINNER_NUMBER 5


// Hardware specific config
#if defined(LITEPOG_EXP430)  // MSP-EXP430FR5739

// Neopixel is driven by UCB0
#define NPX_UCxCTLW0 UCB0CTLW0
#define NPX_UCxBR0   UCB0BR0
#define NPX_UCxTXBUF UCB0TXBUF
#define NPX_UCxSTATW UCB0STATW
#define NPX_UCxIFG   UCB0IFG

// Neopixel data pin is P1.6 (UCB0SIMO)
#define NPX_PxDIR  P1DIR
#define NPX_PxSEL0 P1SEL0
#define NPX_PxSEL1 P1SEL1
#define NPX_PIN    BIT6

// UCB0 SPI clock pin is P2.2 (used for timing debug)
#define NPX_DBG_CLK_PxDIR  P2DIR
#define NPX_DBG_CLK_PxSEL0 P2SEL0
#define NPX_DBG_CLK_PxSEL1 P2SEL1
#define NPX_DBG_CLK_PIN    BIT2

// Buttons are connected to P4
#define BTN_PxDIR P4DIR
#define BTN_PxIN  P4IN
// Button 1 (connected to logic handle) is on P4.0
#define BTN1_PIN BIT0
// Button 2 (connected to power handle) is on P4.1
#define BTN2_PIN BIT1

// EXP430 board requires internal pullups
#define BTN_PULLUP_EN
#define BTN_PxREN P4REN
#define BTN_PxOUT P4OUT

// LEDs are connected to PJ
#define LED_PxDIR PJDIR
#define LED_PxOUT PJOUT
// LED 1 (connected to logic handle) is on PJ.0
#define LED1_PIN BIT0
// LED 2 (connected to power handle) is on PJ.1
#define LED2_PIN BIT1

#elif defined(LITEPOG_MAIN)  // LitePog mainboard (default config)

// Neopixel is driven by UCB0
#define NPX_UCxCTLW0 UCB0CTLW0
#define NPX_UCxBR0   UCB0BR0
#define NPX_UCxTXBUF UCB0TXBUF
#define NPX_UCxSTATW UCB0STATW
#define NPX_UCxIFG   UCB0IFG

// Neopixel data pin is P1.6 (UCB0SIMO)
#define NPX_PxDIR  P1DIR
#define NPX_PxSEL0 P1SEL0
#define NPX_PxSEL1 P1SEL1
#define NPX_PIN    BIT6

// UCB0 SPI clock pin is P2.2 (used for timing debug)
#define NPX_DBG_CLK_PxDIR  P2DIR
#define NPX_DBG_CLK_PxSEL0 P2SEL0
#define NPX_DBG_CLK_PxSEL1 P2SEL1
#define NPX_DBG_CLK_PIN    BIT2

// Buttons are connected to P3
#define BTN_PxDIR P3DIR
#define BTN_PxIN  P3IN
// Button 1 (connected to logic handle) is on P3.0
#define BTN1_PIN BIT0
// Button 2 (connected to power handle) is on P3.1
#define BTN2_PIN BIT1

// LEDs are connected to PJ
#define LED_PxDIR PJDIR
#define LED_PxOUT PJOUT
// LED 1 (connected to logic handle) is on PJ.0
#define LED1_PIN BIT0
// LED 2 (connected to power handle) is on PJ.1
#define LED2_PIN BIT1

#elif defined(LITEPOG_ALT)  // LitePog mainboard (alt config)

// Neopixel is driven by UCA0
#define NPX_UCxCTLW0 UCA0CTLW0
#define NPX_UCxBR0   UCA0BR0
#define NPX_UCxTXBUF UCA0TXBUF
#define NPX_UCxSTATW UCA0STATW
#define NPX_UCxIFG   UCA0IFG

// Neopixel data pin is P2.0 (UCA0SIMO)
#define NPX_PxDIR  P2DIR
#define NPX_PxSEL0 P2SEL0
#define NPX_PxSEL1 P2SEL1
#define NPX_PIN    BIT0

// UCA0 SPI clock pin is P1.5 (used for timing debug)
#define NPX_DBG_CLK_PxDIR  P1DIR
#define NPX_DBG_CLK_PxSEL0 P1SEL0
#define NPX_DBG_CLK_PxSEL1 P1SEL1
#define NPX_DBG_CLK_PIN    BIT5

// Buttons are connected to P3
#define BTN_PxDIR P3DIR
#define BTN_PxIN  P3IN
// Button 1 (connected to logic handle) is on P3.2
#define BTN1_PIN BIT2
// Button 2 (connected to power handle) is on P3.3
#define BTN2_PIN BIT3

// LEDs are connected to PJ
#define LED_PxDIR PJDIR
#define LED_PxOUT PJOUT
// LED 1 (connected to logic handle) is on PJ.2
#define LED1_PIN BIT2
// LED 2 (connected to power handle) is on PJ.3
#define LED2_PIN BIT3

#else

#error A proper configuration must be defined

#endif


#endif /* CONFIG_H_ */
